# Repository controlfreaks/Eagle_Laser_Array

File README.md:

# Eagle_Laser_Array
Repository for project, 'Laser Array' Eagle files.

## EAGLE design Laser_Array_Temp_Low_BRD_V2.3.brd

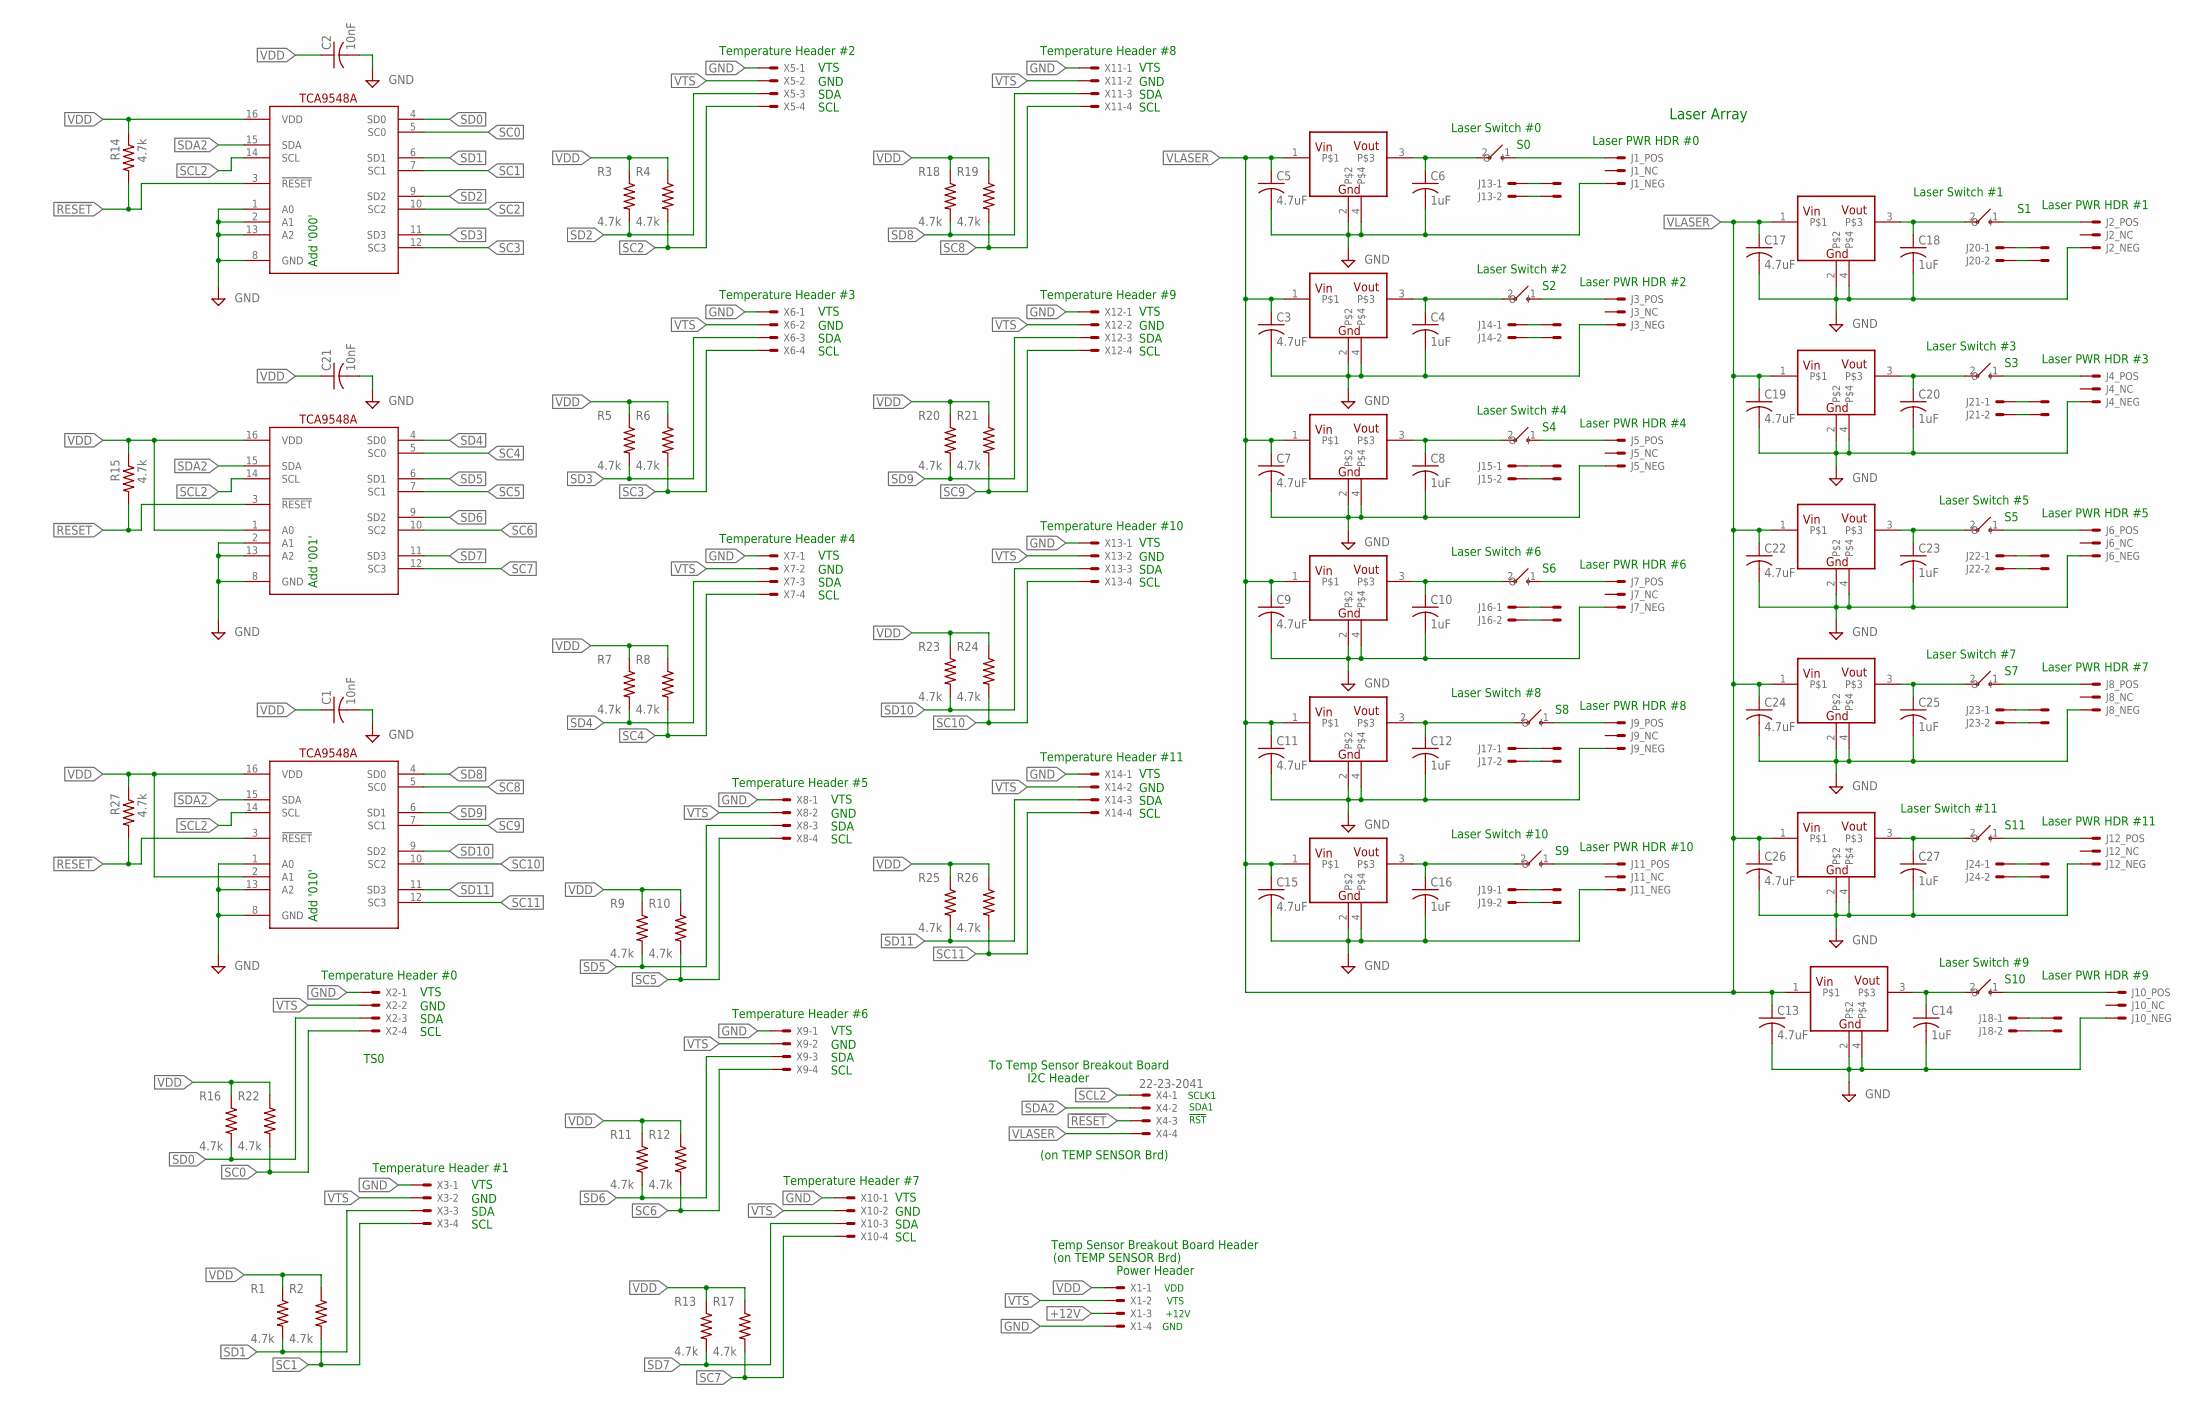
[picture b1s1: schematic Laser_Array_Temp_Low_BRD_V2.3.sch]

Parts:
C1, C2, C21: 10nF; C0805
C3, C5, C7, C9, C11, C13, C15, C17, C19, C22, C24, C26: 4.7uF; C0805
C4, C6, C8, C10, C12, C14, C16, C18, C20, C23, C25, C27: 1uF; C0805
J1, J2, J3, J4, J5, J6, J7, J8, J9, J10, J11, J12: LASER_MOD
J13, J14, J15, J16, J17, J18, J19, J20, J21, J22, J23, J24: 22-23-2021
R1, R2, R3, R4, R5, R6, R7, R8, R9, R10, R11, R12, R13, R14, R15, R16, R17, R18, R19, R20, R21, R22, R23, R24, R25, R26, R27: 4.7k; M0805
S13, S14, S15, S16, S17, S18, S19, S20, S21, S22, S23, S24: TOGGLE_SPST; 22-23-2021
U1, U2, U3: TCA9546A; SOIC16N
U4, U5, U6, U7, U8, U9, U10, U11, U12, U13, U14, U15: V_REG_3.0V_1.0A; SOT223
U$1, U$2, U$4, U$5, U$7, U$8, U$10, U$11, U$13, U$14, U$16, U$17, U$19, U$20, U$22, U$23, U$25, U$26, U$28, U$29, U$31, U$32, U$34, U$35: SINGLE_PAD
X1, X2, X3, X4, X5, X6, X7, X8, X9, X10, X11, X12, X13, X14: 22-23-2041

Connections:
!RESET: R14.2, R15.2, R27.2, U1.3 (!RESET), U2.3 (!RESET), U3.3 (!RESET), X4.3
+12V: X1.3
GND: C1.2, C2.2, C3.2, C4.2, C5.2, C6.2, C7.2, C8.2, C9.2, C10.2, C11.2, C12.2, C13.2, C14.2, C15.2, C16.2, C17.2, C18.2, C19.2, C20.2, C21.2, C22.2, C23.2, C24.2, C25.2, C26.2, C27.2, J1.3, J2.3, J3.3, J4.3, J5.3, J6.3, J7.3, J8.3, J9.3, J10.3, J11.3, J12.3, U1.1 (A0), U1.2 (A1), U1.8 (GND), U1.13 (A2), U2.2 (A1), U2.8 (GND), U2.13 (A2), U3.1 (A0), U3.8 (GND), U3.13 (A2), U4.2, U4.4, U5.2, U5.4, U6.2, U6.4, U7.2, U7.4, U8.2, U8.4, U9.2, U9.4, U10.2, U10.4, U11.2, U11.4, U12.2, U12.4, U13.2, U13.4, U14.2, U14.4, U15.2, U15.4, X1.4, X2.1, X3.1, X5.1, X6.1, X7.1, X8.1, X9.1, X10.1, X11.1, X12.1, X13.1, X14.1
unnamed: J2.1, S13.1 (O)
unnamed: J1.1, S16.1 (O)
unnamed: J3.1, S14.1 (O)
unnamed: J4.1, S15.1 (O)
unnamed: J5.1, S17.1 (O)
unnamed: J6.1, S18.1 (O)
unnamed: J7.1, S19.1 (O)
unnamed: J8.1, S20.1 (O)
unnamed: J9.1, S21.1 (O)
unnamed: J11.1, S23.1 (O)
unnamed: J10.1, S22.1 (O)
unnamed: J12.1, S24.1 (O)
unnamed: J14.1, U$4.1
unnamed: J13.1, U$1.1
unnamed: J21.1, U$10.1
unnamed: J15.1, U$13.1
unnamed: J20.1, U$7.1
unnamed: J22.1, U$16.1
unnamed: J16.1, U$19.1
unnamed: J13.2, U$2.1
unnamed: C8.1, S17.2 (I), U6.3
unnamed: J14.2, U$5.1
unnamed: C4.1, S14.2 (I), U4.3
unnamed: J20.2, U$8.1
unnamed: C20.1, S15.2 (I), U12.3
unnamed: J21.2, U$11.1
unnamed: C25.1, S20.2 (I), U14.3
unnamed: J15.2, U$14.1
unnamed: C10.1, S19.2 (I), U7.3
unnamed: J22.2, U$17.1
unnamed: C23.1, S18.2 (I), U13.3
unnamed: J16.2, U$20.1
unnamed: C12.1, S21.2 (I), U8.3
unnamed: J23.1, U$22.1
unnamed: J23.2, U$23.1
unnamed: C27.1, S24.2 (I), U15.3
unnamed: J17.1, U$25.1
unnamed: J17.2, U$26.1
unnamed: C14.1, S22.2 (I), U9.3
unnamed: J18.1, U$28.1
unnamed: J18.2, U$29.1
unnamed: J24.1, U$31.1
unnamed: J24.2, U$32.1
unnamed: J19.1, U$34.1
unnamed: J19.2, U$35.1
unnamed: C18.1, S13.2 (I), U11.3
unnamed: C16.1, S23.2 (I), U10.3
unnamed: C6.1, S16.2 (I), U5.3
SC0: R22.2, U1.5 (SC0), X2.4
SC1: R2.2, U1.7 (SC1), X3.4
SC2: R4.2, U1.10 (SC2), X5.4
SC3: R6.2, U1.12 (SC3), X6.4
SC4: R8.2, U2.5 (SC0), X7.4
SC5: R10.2, U2.7 (SC1), X8.4
SC6: R12.2, U2.10 (SC2), X9.4
SC7: R17.2, U2.12 (SC3), X10.4
SC8: R19.2, U3.5 (SC0), X11.4
SC9: R21.2, U3.7 (SC1), X12.4
SC10: R24.2, U3.10 (SC2), X13.4
SC11: R26.2, U3.12 (SC3), X14.4
SCL2: U1.14 (SCL), U2.14 (SCL), U3.14 (SCL), X4.1
SD0: R16.2, U1.4 (SD0), X2.3
SD1: R1.2, U1.6 (SD1), X3.3
SD2: R3.2, U1.9 (SD2), X5.3
SD3: R5.2, U1.11 (SD3), X6.3
SD4: R7.2, U2.4 (SD0), X7.3
SD5: R9.2, U2.6 (SD1), X8.3
SD6: R11.2, U2.9 (SD2), X9.3
SD7: R13.2, U2.11 (SD3), X10.3
SD8: R18.2, U3.4 (SD0), X11.3
SD9: R20.2, U3.6 (SD1), X12.3
SD10: R23.2, U3.9 (SD2), X13.3
SD11: R25.2, U3.11 (SD3), X14.3
SDA2: U1.15 (SDA), U2.15 (SDA), U3.15 (SDA), X4.2
VDD: C1.1, C2.1, C21.1, R1.1, R2.1, R3.1, R4.1, R5.1, R6.1, R7.1, R8.1, R9.1, R10.1, R11.1, R12.1, R13.1, R14.1, R15.1, R16.1, R17.1, R18.1, R19.1, R20.1, R21.1, R22.1, R23.1, R24.1, R25.1, R26.1, R27.1, U1.16 (VDD), U2.1 (A0), U2.16 (VDD), U3.2 (A1), U3.16 (VDD), X1.1
VLASER: C3.1, C5.1, C7.1, C9.1, C11.1, C13.1, C15.1, C17.1, C19.1, C22.1, C24.1, C26.1, U4.1, U5.1, U6.1, U7.1, U8.1, U9.1, U10.1, U11.1, U12.1, U13.1, U14.1, U15.1, X4.4
VTS: X1.2, X2.2, X3.2, X5.2, X6.2, X7.2, X8.2, X9.2, X10.2, X11.2, X12.2, X13.2, X14.2

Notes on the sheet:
TS0
Laser Array
I2C Header
To Temp Sensor Breakout Board
SCLK1
SDA1
!RST
Power Header
VDD
+12V
GND
Temp Sensor Breakout Board Header
VTS
(on TEMP SENSOR Brd)
Temperature Header #0
SDA
SCL
Laser Switch #0
Laser PWR HDR #0
Temperature Header #1
Temperature Header #2
Temperature Header #3
Temperature Header #4
Temperature Header #5
Temperature Header #6
Temperature Header #7
Temperature Header #8
Temperature Header #9
Temperature Header #10
Temperature Header #11
Add '000'
Laser Switch #1
Laser PWR HDR #1
Laser Switch #2
Laser PWR HDR #2
Laser Switch #3
Laser PWR HDR #3
Laser Switch #4
Laser PWR HDR #4
Laser Switch #5

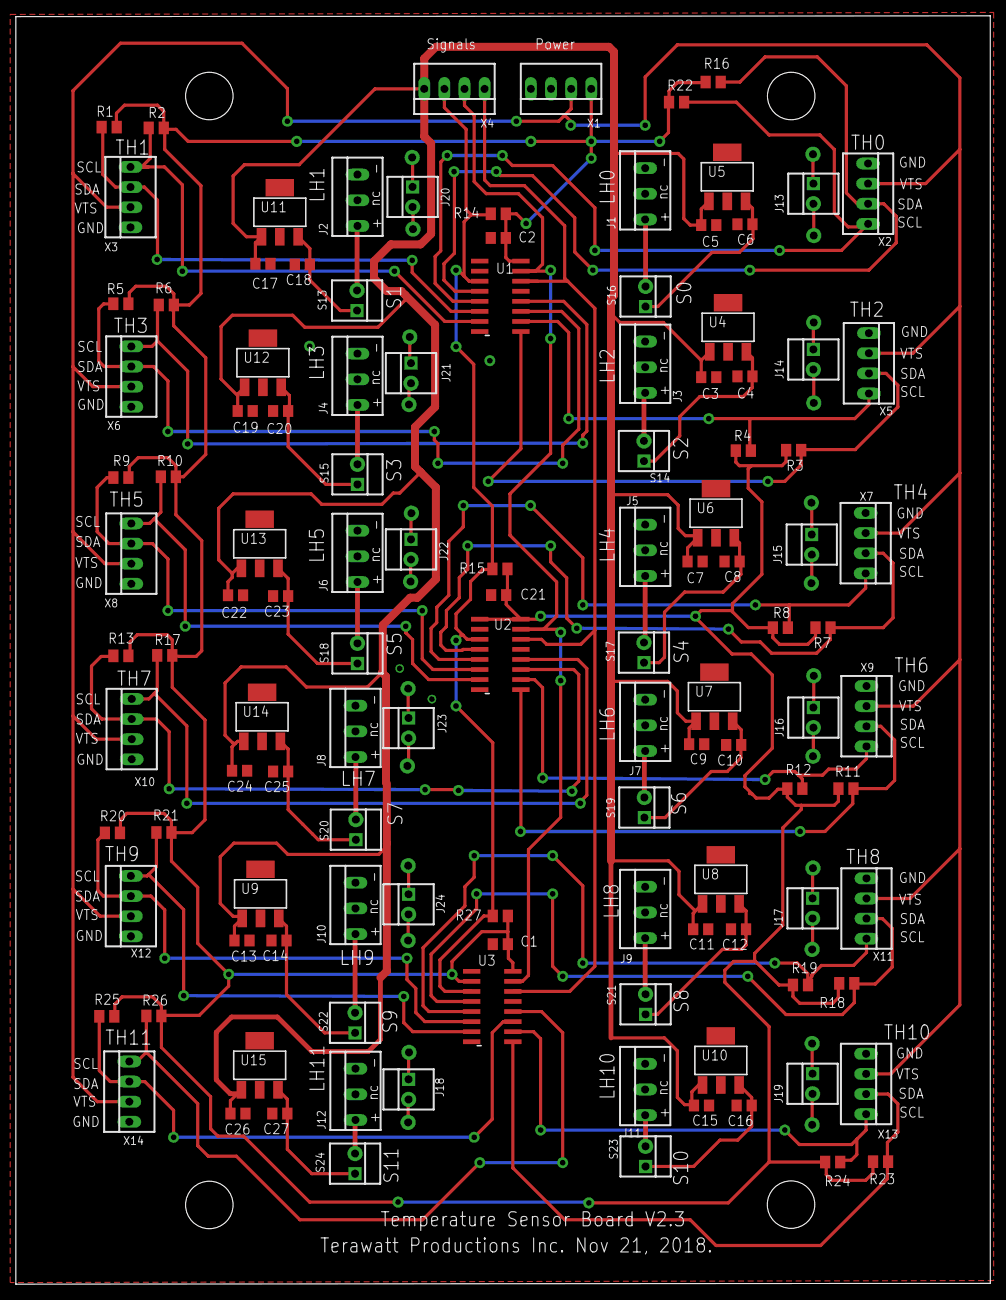
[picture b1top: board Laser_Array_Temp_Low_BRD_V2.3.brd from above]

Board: 2 copper layers, 123.0 x 160.1 mm, 143 parts (0 on the bottom side), 79 nets.

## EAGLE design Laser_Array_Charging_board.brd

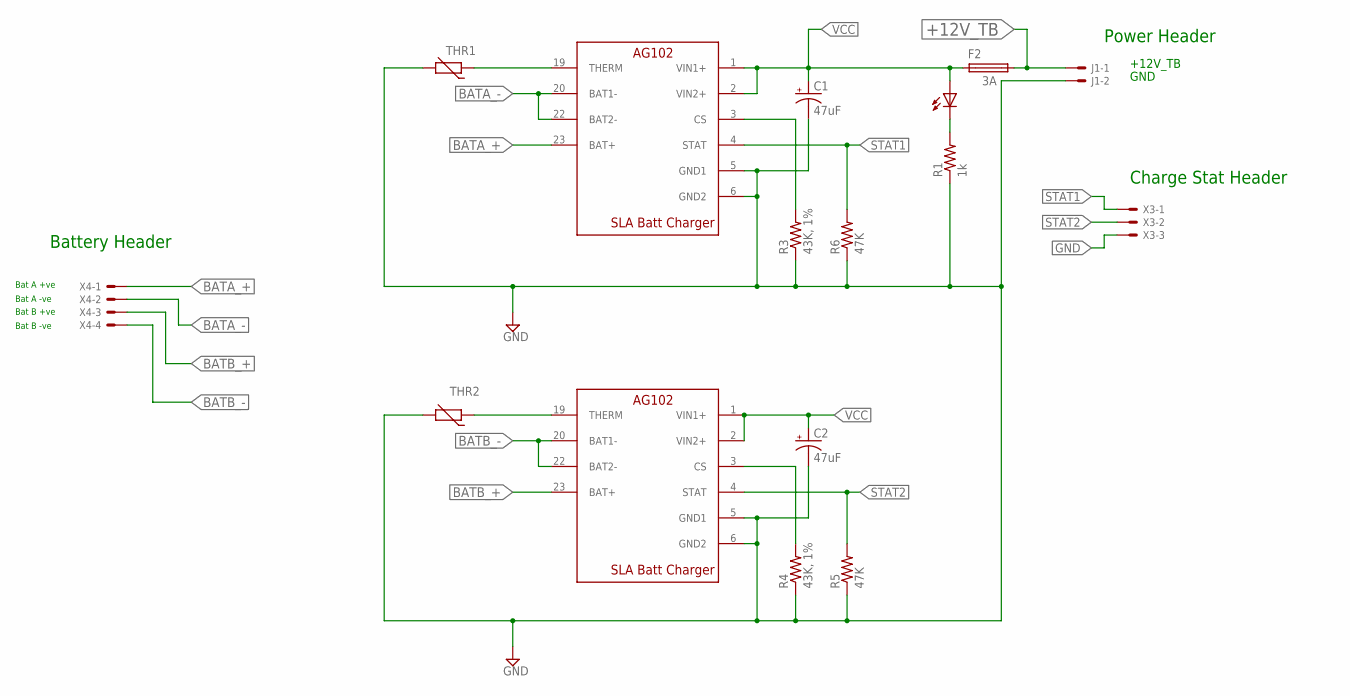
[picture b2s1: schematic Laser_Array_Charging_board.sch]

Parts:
C1, C2: 47uF; E5-10,5
CHG1, CHG2: AG102_SLA_CHARGER; SLA_CHARGER
F2: 3A; SH22,5
J1: 22-23-2021
LED1: LEDCHIPLED_0805; CHIPLED_0805
R1: 1k; M0805
R3, R4: 43K, 1%; R0805
R5, R6: 47K; R0805
THR1, THR2: THERMISTOR-2,5; RS-2,5
X3: 22-23-2031
X4: 22-23-2041

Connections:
+12V_TB: F2.2, J1.1
BATA_+: CHG1.23 (BAT+), X4.1
BATA_-: CHG1.20 (BAT1-), CHG1.22 (BAT2-), X4.2
BATB_+: CHG2.23 (BAT+), X4.3
BATB_-: CHG2.20 (BAT1-), CHG2.22 (BAT2-), X4.4
GND: C1.-, C2.-, CHG1.5 (GND1), CHG1.6 (GND2), CHG2.5 (GND1), CHG2.6 (GND2), J1.2, R1.1, R3.1, R4.1, R5.1, R6.1, THR1.2, THR2.2, X3.3
unnamed: CHG1.19 (THERM), THR1.1
unnamed: CHG2.19 (THERM), THR2.1
unnamed: LED1.C, R1.2
unnamed: CHG1.3 (CS), R3.2
unnamed: CHG2.3 (CS), R4.2
STAT1: CHG1.4 (STAT), R6.2, X3.1
STAT2: CHG2.4 (STAT), R5.2, X3.2
VCC: C1.+, C2.+, CHG1.1 (VIN1+), CHG1.2 (VIN2+), CHG2.1 (VIN1+), CHG2.2 (VIN2+), F2.1, LED1.A

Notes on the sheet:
+12V_TB
GND
Bat A +ve
Bat A -ve
Bat B -ve
Bat B +ve
Battery Header
Power Header
Charge Stat Header

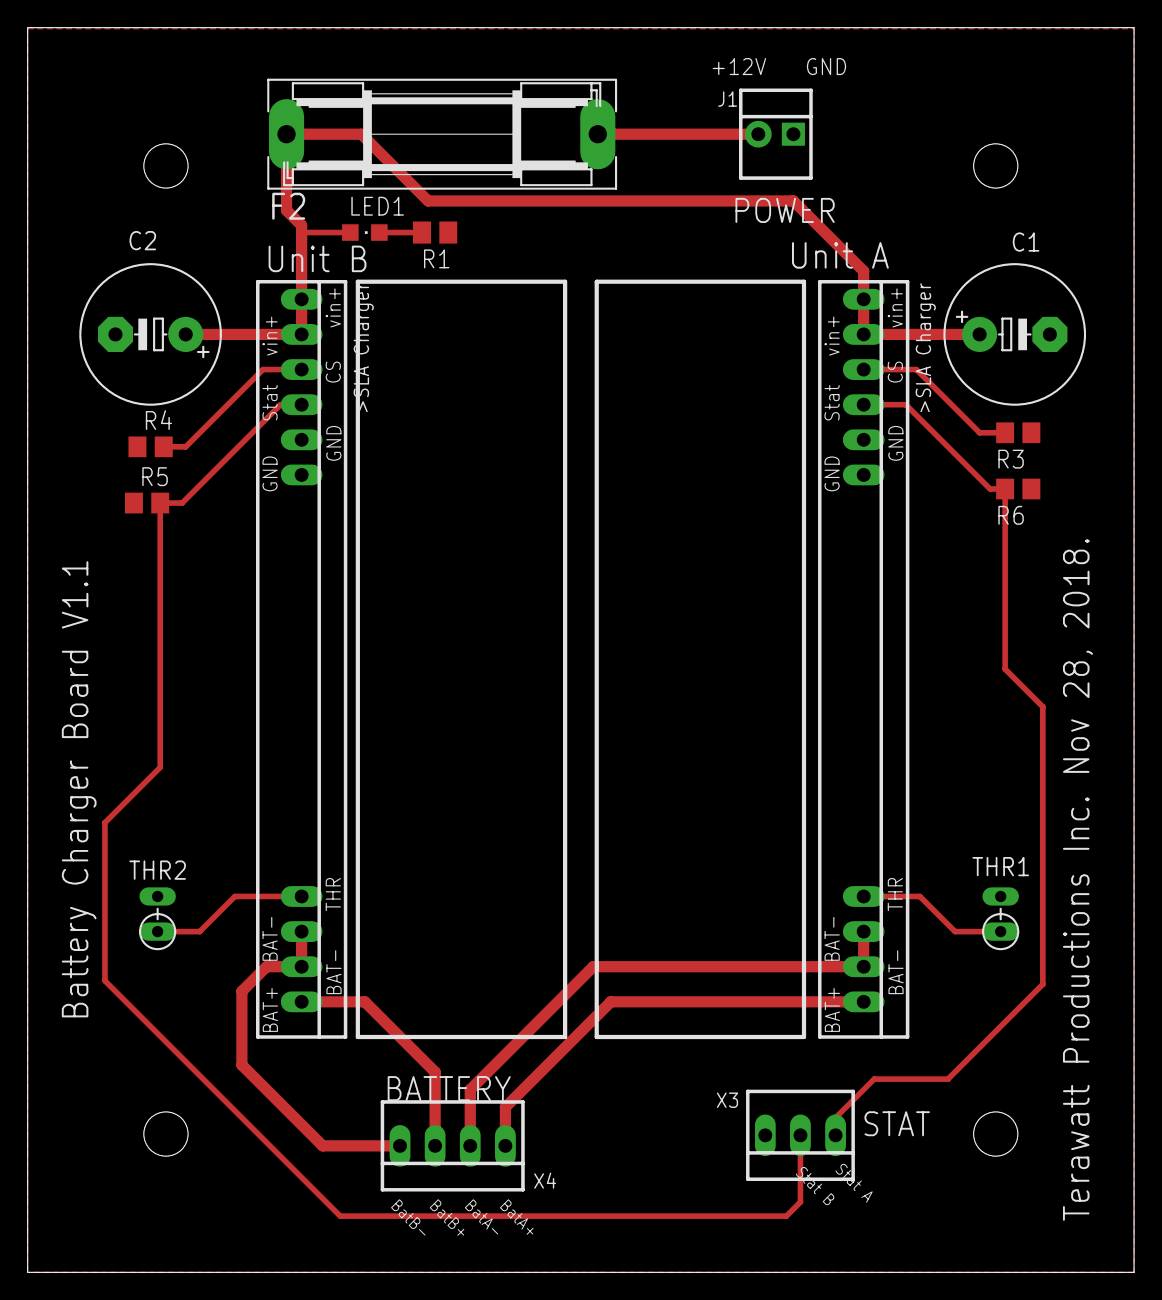
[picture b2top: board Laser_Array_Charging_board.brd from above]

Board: 2 copper layers, 80.0 x 90.0 mm, 16 parts (0 on the bottom side), 14 nets.

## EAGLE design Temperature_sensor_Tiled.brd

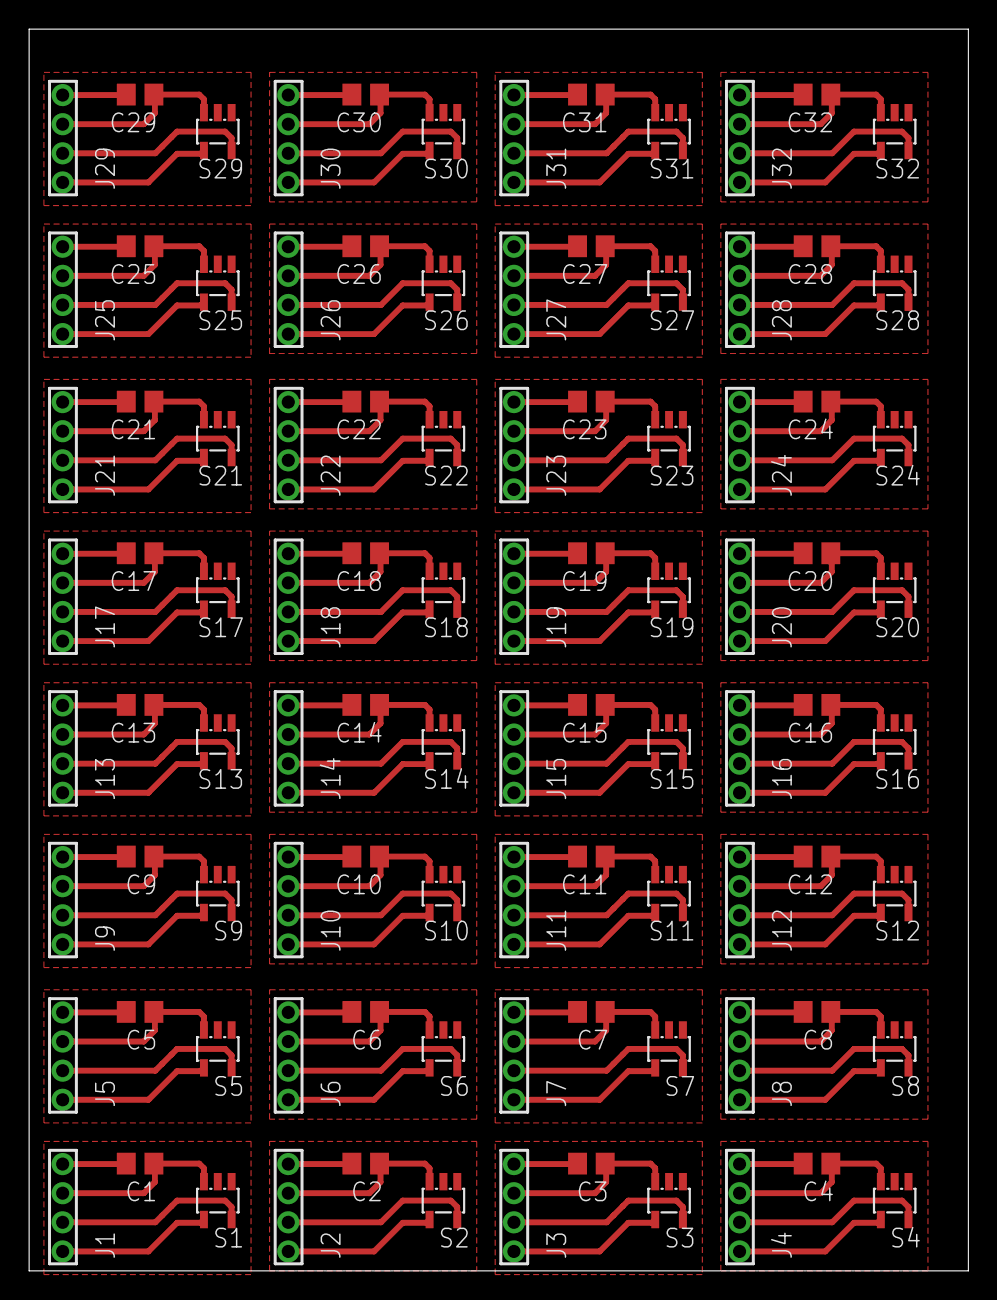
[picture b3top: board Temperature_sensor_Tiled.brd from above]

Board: 2 copper layers, 64.5 x 85.3 mm, 96 parts (0 on the bottom side), 128 nets.

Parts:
C1, C2, C3, C4, C5, C6, C7, C8, C9, C10, C11, C12, C13, C14, C15, C16, C17, C18, C19, C20, C21, C22, C23, C24, C25, C26, C27, C28, C29, C30, C31, C32: 0.01uF; C0805
J1, J2, J3, J4, J5, J6, J7, J8, J9, J10, J11, J12, J13, J14, J15, J16, J17, J18, J19, J20, J21, J22, J23, J24, J25, J26, J27, J28, J29, J30, J31, J32: 4_PIN_2MM; 2MM_4PIN_LARGE
S1, S2, S3, S4, S5, S6, S7, S8, S9, S10, S11, S12, S13, S14, S15, S16, S17, S18, S19, S20, S21, S22, S23, S24, S25, S26, S27, S28, S29, S30, S31, S32: TC74; SOT23-5L

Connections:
GND: C1.2, J1.8, S1.2
GND1: C2.2, J2.8, S2.2
GND2: C3.2, J3.8, S3.2
GND3: C4.2, J4.8, S4.2
GND4: C5.2, J5.8, S5.2
GND5: C6.2, J6.8, S6.2
GND6: C7.2, J7.8, S7.2
GND7: C8.2, J8.8, S8.2
GND8: C9.2, J9.8, S9.2
GND9: C10.2, J10.8, S10.2
GND10: C11.2, J11.8, S11.2
GND11: C12.2, J12.8, S12.2
GND12: C13.2, J13.8, S13.2
GND13: C14.2, J14.8, S14.2
GND14: C15.2, J15.8, S15.2
GND15: C16.2, J16.8, S16.2
GND16: C17.2, J17.8, S17.2
GND17: C18.2, J18.8, S18.2
GND18: C19.2, J19.8, S19.2
GND19: C20.2, J20.8, S20.2
GND20: C21.2, J21.8, S21.2
GND21: C22.2, J22.8, S22.2
GND22: C23.2, J23.8, S23.2
GND23: C24.2, J24.8, S24.2
GND24: C25.2, J25.8, S25.2
GND25: C26.2, J26.8, S26.2
GND26: C27.2, J27.8, S27.2
GND27: C28.2, J28.8, S28.2
GND28: C29.2, J29.8, S29.2
GND29: C30.2, J30.8, S30.2
GND30: C31.2, J31.8, S31.2
GND31: C32.2, J32.8, S32.2
unnamed: J2.4, S2.5
unnamed: C1.1, J1.6, S1.3
unnamed: J1.4, S1.5
unnamed: J1.2, S1.4
unnamed: J2.2, S2.4
unnamed: C2.1, J2.6, S2.3
unnamed: J3.4, S3.5
unnamed: J3.2, S3.4
unnamed: C3.1, J3.6, S3.3
unnamed: J4.4, S4.5
unnamed: J4.2, S4.4
unnamed: C4.1, J4.6, S4.3
unnamed: J5.4, S5.5
unnamed: J5.2, S5.4
unnamed: C5.1, J5.6, S5.3
unnamed: J6.4, S6.5
unnamed: J6.2, S6.4
unnamed: C6.1, J6.6, S6.3
unnamed: J7.4, S7.5
unnamed: J7.2, S7.4
unnamed: C7.1, J7.6, S7.3
unnamed: J8.4, S8.5
unnamed: J8.2, S8.4
unnamed: C8.1, J8.6, S8.3
unnamed: J9.4, S9.5
unnamed: J9.2, S9.4
unnamed: C9.1, J9.6, S9.3
unnamed: J10.4, S10.5
unnamed: J10.2, S10.4
unnamed: C10.1, J10.6, S10.3
unnamed: J11.4, S11.5
unnamed: J11.2, S11.4
unnamed: C11.1, J11.6, S11.3
unnamed: J12.4, S12.5
unnamed: J12.2, S12.4
unnamed: C12.1, J12.6, S12.3
unnamed: J13.4, S13.5
unnamed: J13.2, S13.4
unnamed: C13.1, J13.6, S13.3
unnamed: J14.4, S14.5
unnamed: J14.2, S14.4
unnamed: C14.1, J14.6, S14.3
unnamed: J15.4, S15.5
unnamed: J15.2, S15.4
unnamed: C15.1, J15.6, S15.3
unnamed: J16.4, S16.5
unnamed: J16.2, S16.4
unnamed: C16.1, J16.6, S16.3
unnamed: J17.4, S17.5
unnamed: J17.2, S17.4
unnamed: C17.1, J17.6, S17.3
unnamed: J18.4, S18.5
unnamed: J18.2, S18.4
unnamed: C18.1, J18.6, S18.3
unnamed: J19.4, S19.5
unnamed: J19.2, S19.4
unnamed: C19.1, J19.6, S19.3
unnamed: J20.4, S20.5
unnamed: J20.2, S20.4
unnamed: C20.1, J20.6, S20.3
unnamed: J21.4, S21.5
unnamed: J21.2, S21.4
unnamed: C21.1, J21.6, S21.3
unnamed: J22.4, S22.5
unnamed: J22.2, S22.4
unnamed: C22.1, J22.6, S22.3
unnamed: J23.4, S23.5
unnamed: J23.2, S23.4
unnamed: C23.1, J23.6, S23.3
unnamed: J24.4, S24.5
unnamed: J24.2, S24.4
unnamed: C24.1, J24.6, S24.3
unnamed: J25.4, S25.5
unnamed: J25.2, S25.4
unnamed: C25.1, J25.6, S25.3
unnamed: J26.4, S26.5
unnamed: J26.2, S26.4
unnamed: C26.1, J26.6, S26.3
unnamed: J27.4, S27.5
unnamed: J27.2, S27.4
unnamed: C27.1, J27.6, S27.3
unnamed: J28.4, S28.5
unnamed: J28.2, S28.4
unnamed: C28.1, J28.6, S28.3
unnamed: J29.4, S29.5
unnamed: J29.2, S29.4
unnamed: C29.1, J29.6, S29.3
unnamed: J30.4, S30.5
unnamed: J30.2, S30.4
unnamed: C30.1, J30.6, S30.3
unnamed: J31.4, S31.5
unnamed: J31.2, S31.4
unnamed: C31.1, J31.6, S31.3
unnamed: J32.4, S32.5
unnamed: J32.2, S32.4
unnamed: C32.1, J32.6, S32.3

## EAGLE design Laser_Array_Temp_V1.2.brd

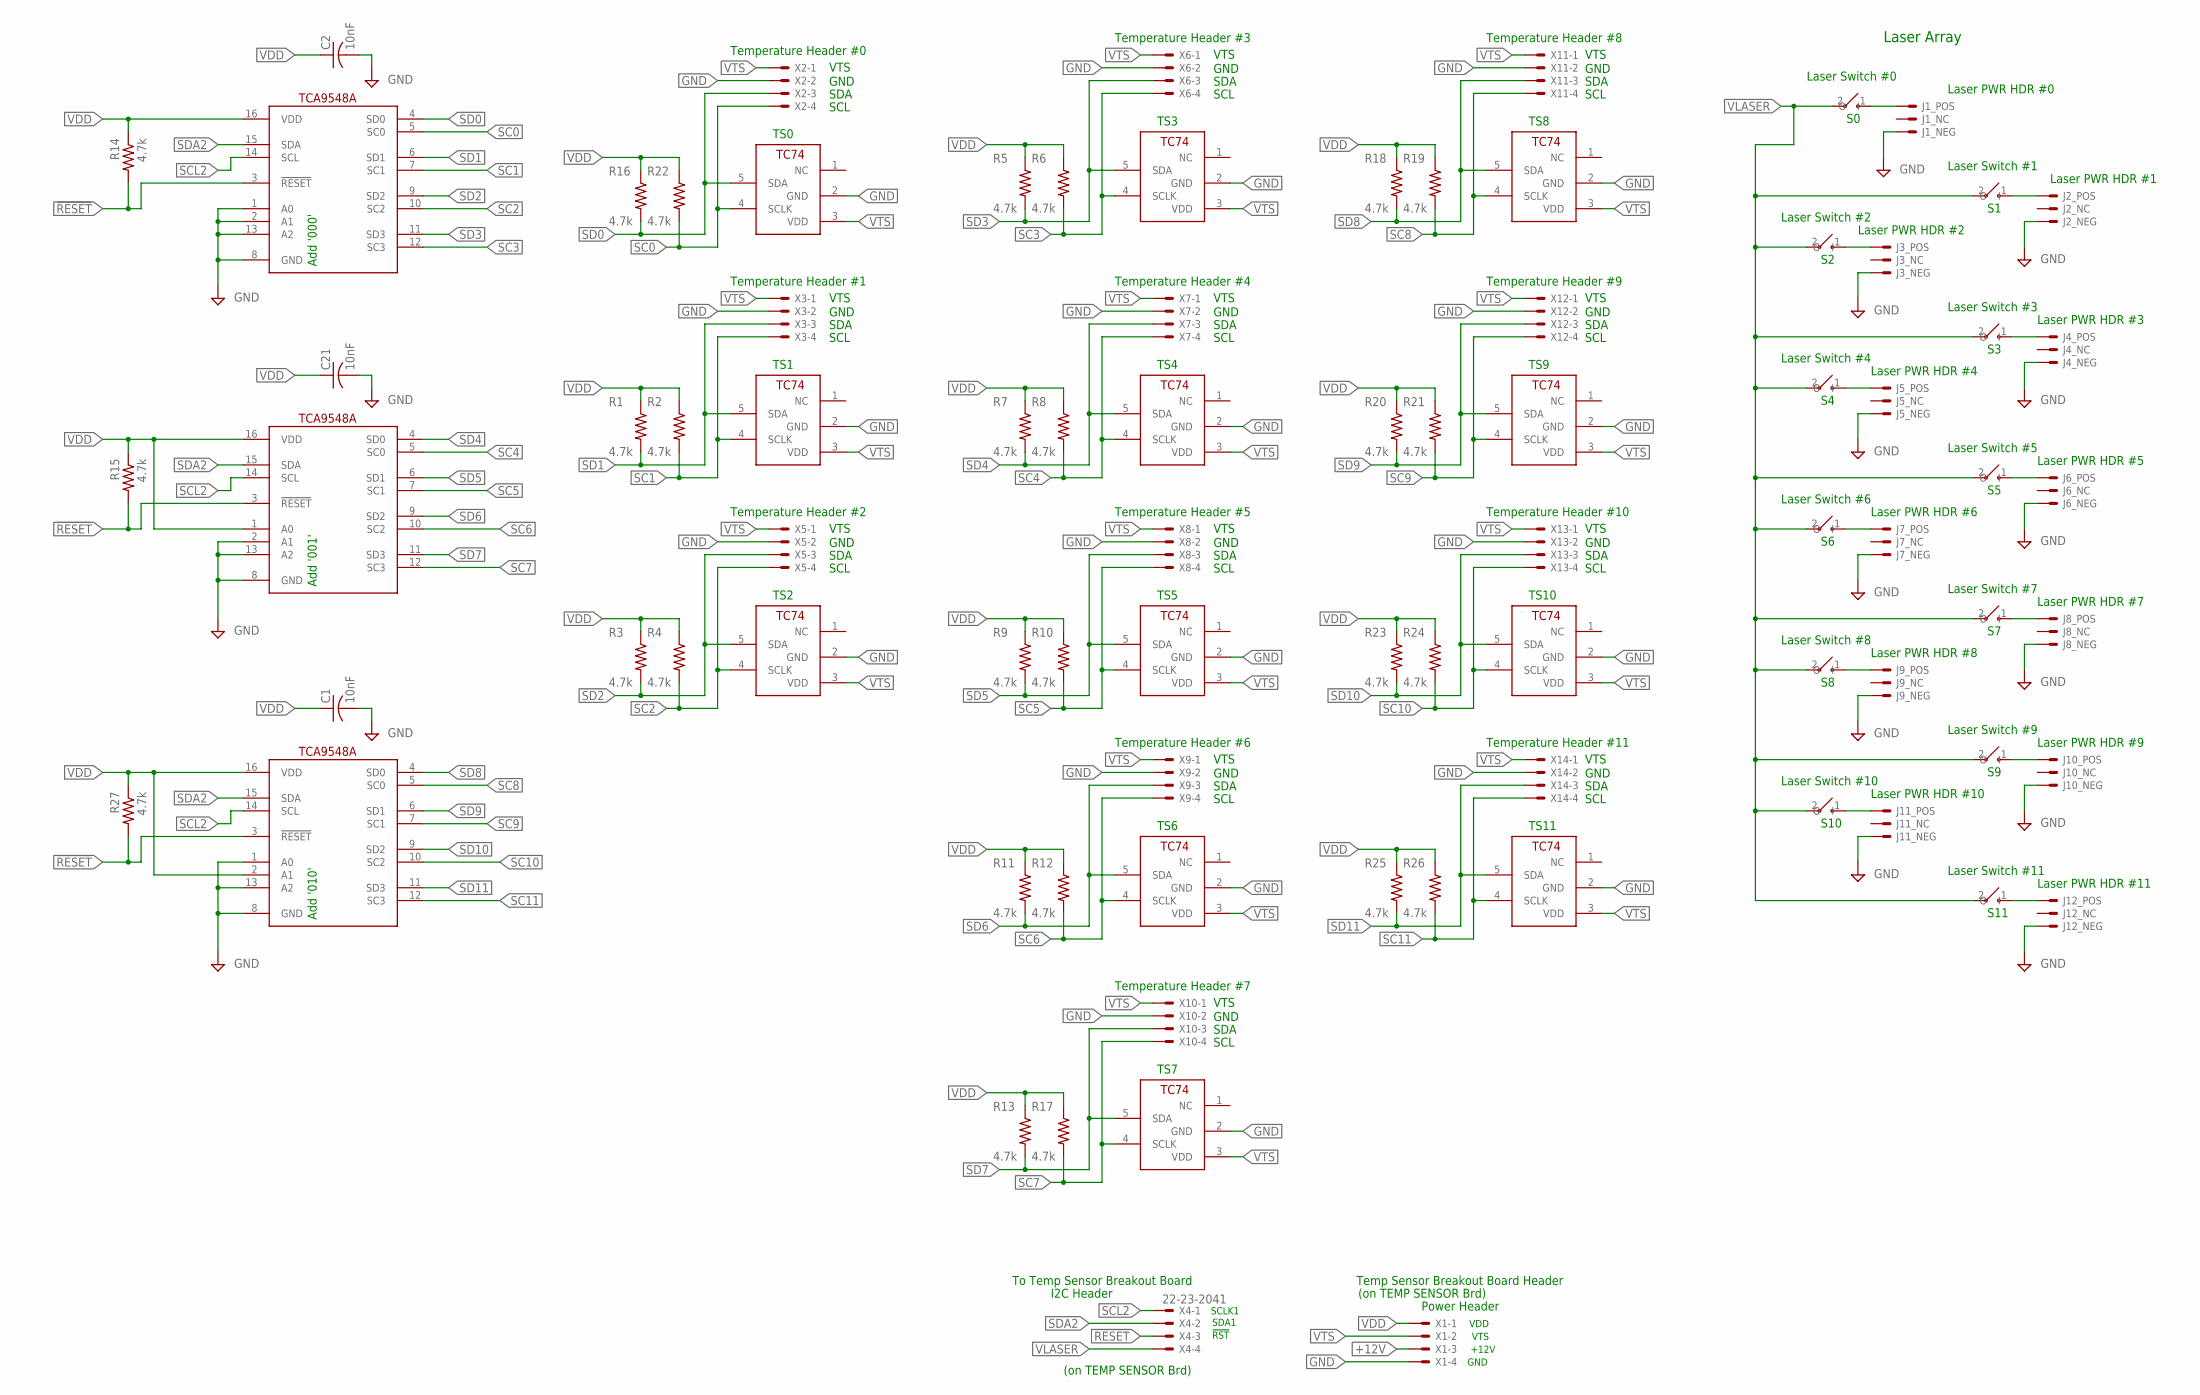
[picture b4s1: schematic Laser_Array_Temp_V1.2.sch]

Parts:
C1, C2, C21: 10nF; C0805
J1, J2, J3, J4, J5, J6, J7, J8, J9, J10, J11, J12: LASER_MOD
R1, R2, R3, R4, R5, R6, R7, R8, R9, R10, R11, R12, R13, R14, R15, R16, R17, R18, R19, R20, R21, R22, R23, R24, R25, R26, R27: 4.7k; M0805
S13, S14, S15, S16, S17, S18, S19, S20, S21, S22, S23, S24: TOGGLE_SPST; 22-23-2021
TS1, TS2, TS3, TS4, TS5, TS6, TS7, TS8, TS9, TS10, TS11, TS12: TC74; SOT23-5L
U1, U2, U3: TCA9546A; SOIC16N
X1, X2, X3, X4, X5, X6, X7, X8, X9, X10, X11, X12, X13, X14: 22-23-2041

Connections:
!RESET: R14.2, R15.2, R27.2, U1.3 (!RESET), U2.3 (!RESET), U3.3 (!RESET), X4.3
+12V: X1.3
GND: C1.2, C2.2, C21.2, J1.3, J2.3, J3.3, J4.3, J5.3, J6.3, J7.3, J8.3, J9.3, J10.3, J11.3, J12.3, TS1.2 (GND), TS2.2 (GND), TS3.2 (GND), TS4.2 (GND), TS5.2 (GND), TS6.2 (GND), TS7.2 (GND), TS8.2 (GND), TS9.2 (GND), TS10.2 (GND), TS11.2 (GND), TS12.2 (GND), U1.1 (A0), U1.2 (A1), U1.8 (GND), U1.13 (A2), U2.2 (A1), U2.8 (GND), U2.13 (A2), U3.1 (A0), U3.8 (GND), U3.13 (A2), X1.4, X2.2, X3.2, X5.2, X6.2, X7.2, X8.2, X9.2, X10.2, X11.2, X12.2, X13.2, X14.2
unnamed: J2.1, S13.1 (O)
unnamed: J1.1, S16.1 (O)
unnamed: J3.1, S14.1 (O)
unnamed: J4.1, S15.1 (O)
unnamed: J5.1, S17.1 (O)
unnamed: J6.1, S18.1 (O)
unnamed: J7.1, S19.1 (O)
unnamed: J8.1, S20.1 (O)
unnamed: J9.1, S21.1 (O)
unnamed: J10.1, S22.1 (O)
unnamed: J11.1, S23.1 (O)
unnamed: J12.1, S24.1 (O)
SC0: R22.2, TS1.4 (SCLK), U1.5 (SC0), X2.4
SC1: R2.2, TS2.4 (SCLK), U1.7 (SC1), X3.4
SC2: R4.2, TS3.4 (SCLK), U1.10 (SC2), X5.4
SC3: R6.2, TS4.4 (SCLK), U1.12 (SC3), X6.4
SC4: R8.2, TS5.4 (SCLK), U2.5 (SC0), X7.4
SC5: R10.2, TS6.4 (SCLK), U2.7 (SC1), X8.4
SC6: R12.2, TS7.4 (SCLK), U2.10 (SC2), X9.4
SC7: R17.2, TS8.4 (SCLK), U2.12 (SC3), X10.4
SC8: R19.2, TS9.4 (SCLK), U3.5 (SC0), X11.4
SC9: R21.2, TS10.4 (SCLK), U3.7 (SC1), X12.4
SC10: R24.2, TS11.4 (SCLK), U3.10 (SC2), X13.4
SC11: R26.2, TS12.4 (SCLK), U3.12 (SC3), X14.4
SCL2: U1.14 (SCL), U2.14 (SCL), U3.14 (SCL), X4.1
SD0: R16.2, TS1.5 (SDA), U1.4 (SD0), X2.3
SD1: R1.2, TS2.5 (SDA), U1.6 (SD1), X3.3
SD2: R3.2, TS3.5 (SDA), U1.9 (SD2), X5.3
SD3: R5.2, TS4.5 (SDA), U1.11 (SD3), X6.3
SD4: R7.2, TS5.5 (SDA), U2.4 (SD0), X7.3
SD5: R9.2, TS6.5 (SDA), U2.6 (SD1), X8.3
SD6: R11.2, TS7.5 (SDA), U2.9 (SD2), X9.3
SD7: R13.2, TS8.5 (SDA), U2.11 (SD3), X10.3
SD8: R18.2, TS9.5 (SDA), U3.4 (SD0), X11.3
SD9: R20.2, TS10.5 (SDA), U3.6 (SD1), X12.3
SD10: R23.2, TS11.5 (SDA), U3.9 (SD2), X13.3
SD11: R25.2, TS12.5 (SDA), U3.11 (SD3), X14.3
SDA2: U1.15 (SDA), U2.15 (SDA), U3.15 (SDA), X4.2
VDD: C1.1, C2.1, C21.1, R1.1, R2.1, R3.1, R4.1, R5.1, R6.1, R7.1, R8.1, R9.1, R10.1, R11.1, R12.1, R13.1, R14.1, R15.1, R16.1, R17.1, R18.1, R19.1, R20.1, R21.1, R22.1, R23.1, R24.1, R25.1, R26.1, R27.1, U1.16 (VDD), U2.1 (A0), U2.16 (VDD), U3.2 (A1), U3.16 (VDD), X1.1
VLASER: S13.2 (I), S14.2 (I), S15.2 (I), S16.2 (I), S17.2 (I), S18.2 (I), S19.2 (I), S20.2 (I), S21.2 (I), S22.2 (I), S23.2 (I), S24.2 (I), X4.4
VTS: TS1.3 (VDD), TS2.3 (VDD), TS3.3 (VDD), TS4.3 (VDD), TS5.3 (VDD), TS6.3 (VDD), TS7.3 (VDD), TS8.3 (VDD), TS9.3 (VDD), TS10.3 (VDD), TS11.3 (VDD), TS12.3 (VDD), X1.2, X2.1, X3.1, X5.1, X6.1, X7.1, X8.1, X9.1, X10.1, X11.1, X12.1, X13.1, X14.1

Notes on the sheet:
TS0
Laser Array
I2C Header
To Temp Sensor Breakout Board
SCLK1
SDA1
!RST
Power Header
VDD
+12V
GND
Temp Sensor Breakout Board Header
VTS
(on TEMP SENSOR Brd)
Temperature Header #0
SDA
SCL
Laser Switch #0
Laser PWR HDR #0
TS1
Temperature Header #1
TS2
Temperature Header #2
TS3
Temperature Header #3
TS4
Temperature Header #4
TS5
Temperature Header #5
TS6
Temperature Header #6
TS7
Temperature Header #7
TS8
Temperature Header #8
TS9
Temperature Header #9
TS10
Temperature Header #10
TS11

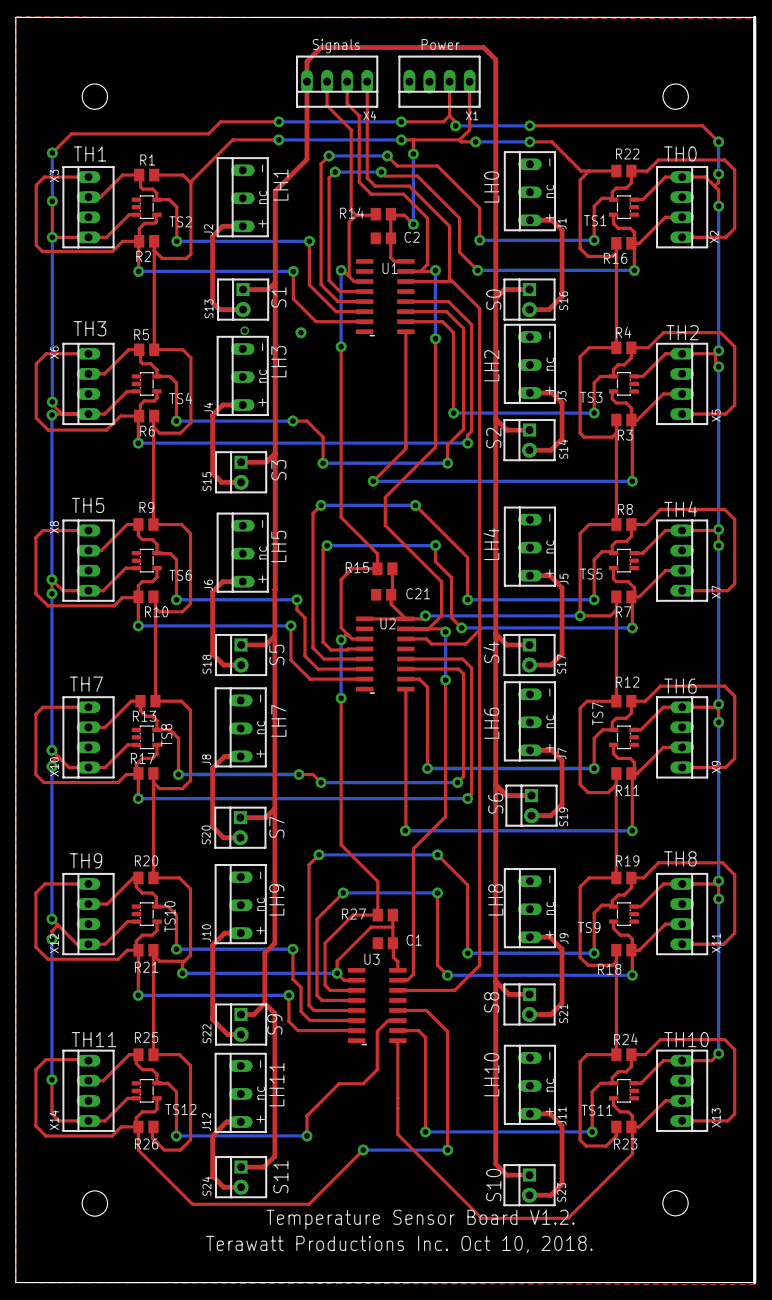
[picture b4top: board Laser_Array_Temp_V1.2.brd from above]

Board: 2 copper layers, 93.5 x 160.0 mm, 83 parts (0 on the bottom side), 43 nets.
